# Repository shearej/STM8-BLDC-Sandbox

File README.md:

# STM8-BLDC-Sandbox
BLDC Project

This is meant as a playground of sorts to be later fully integrated into the Logikos BLDC motor project.

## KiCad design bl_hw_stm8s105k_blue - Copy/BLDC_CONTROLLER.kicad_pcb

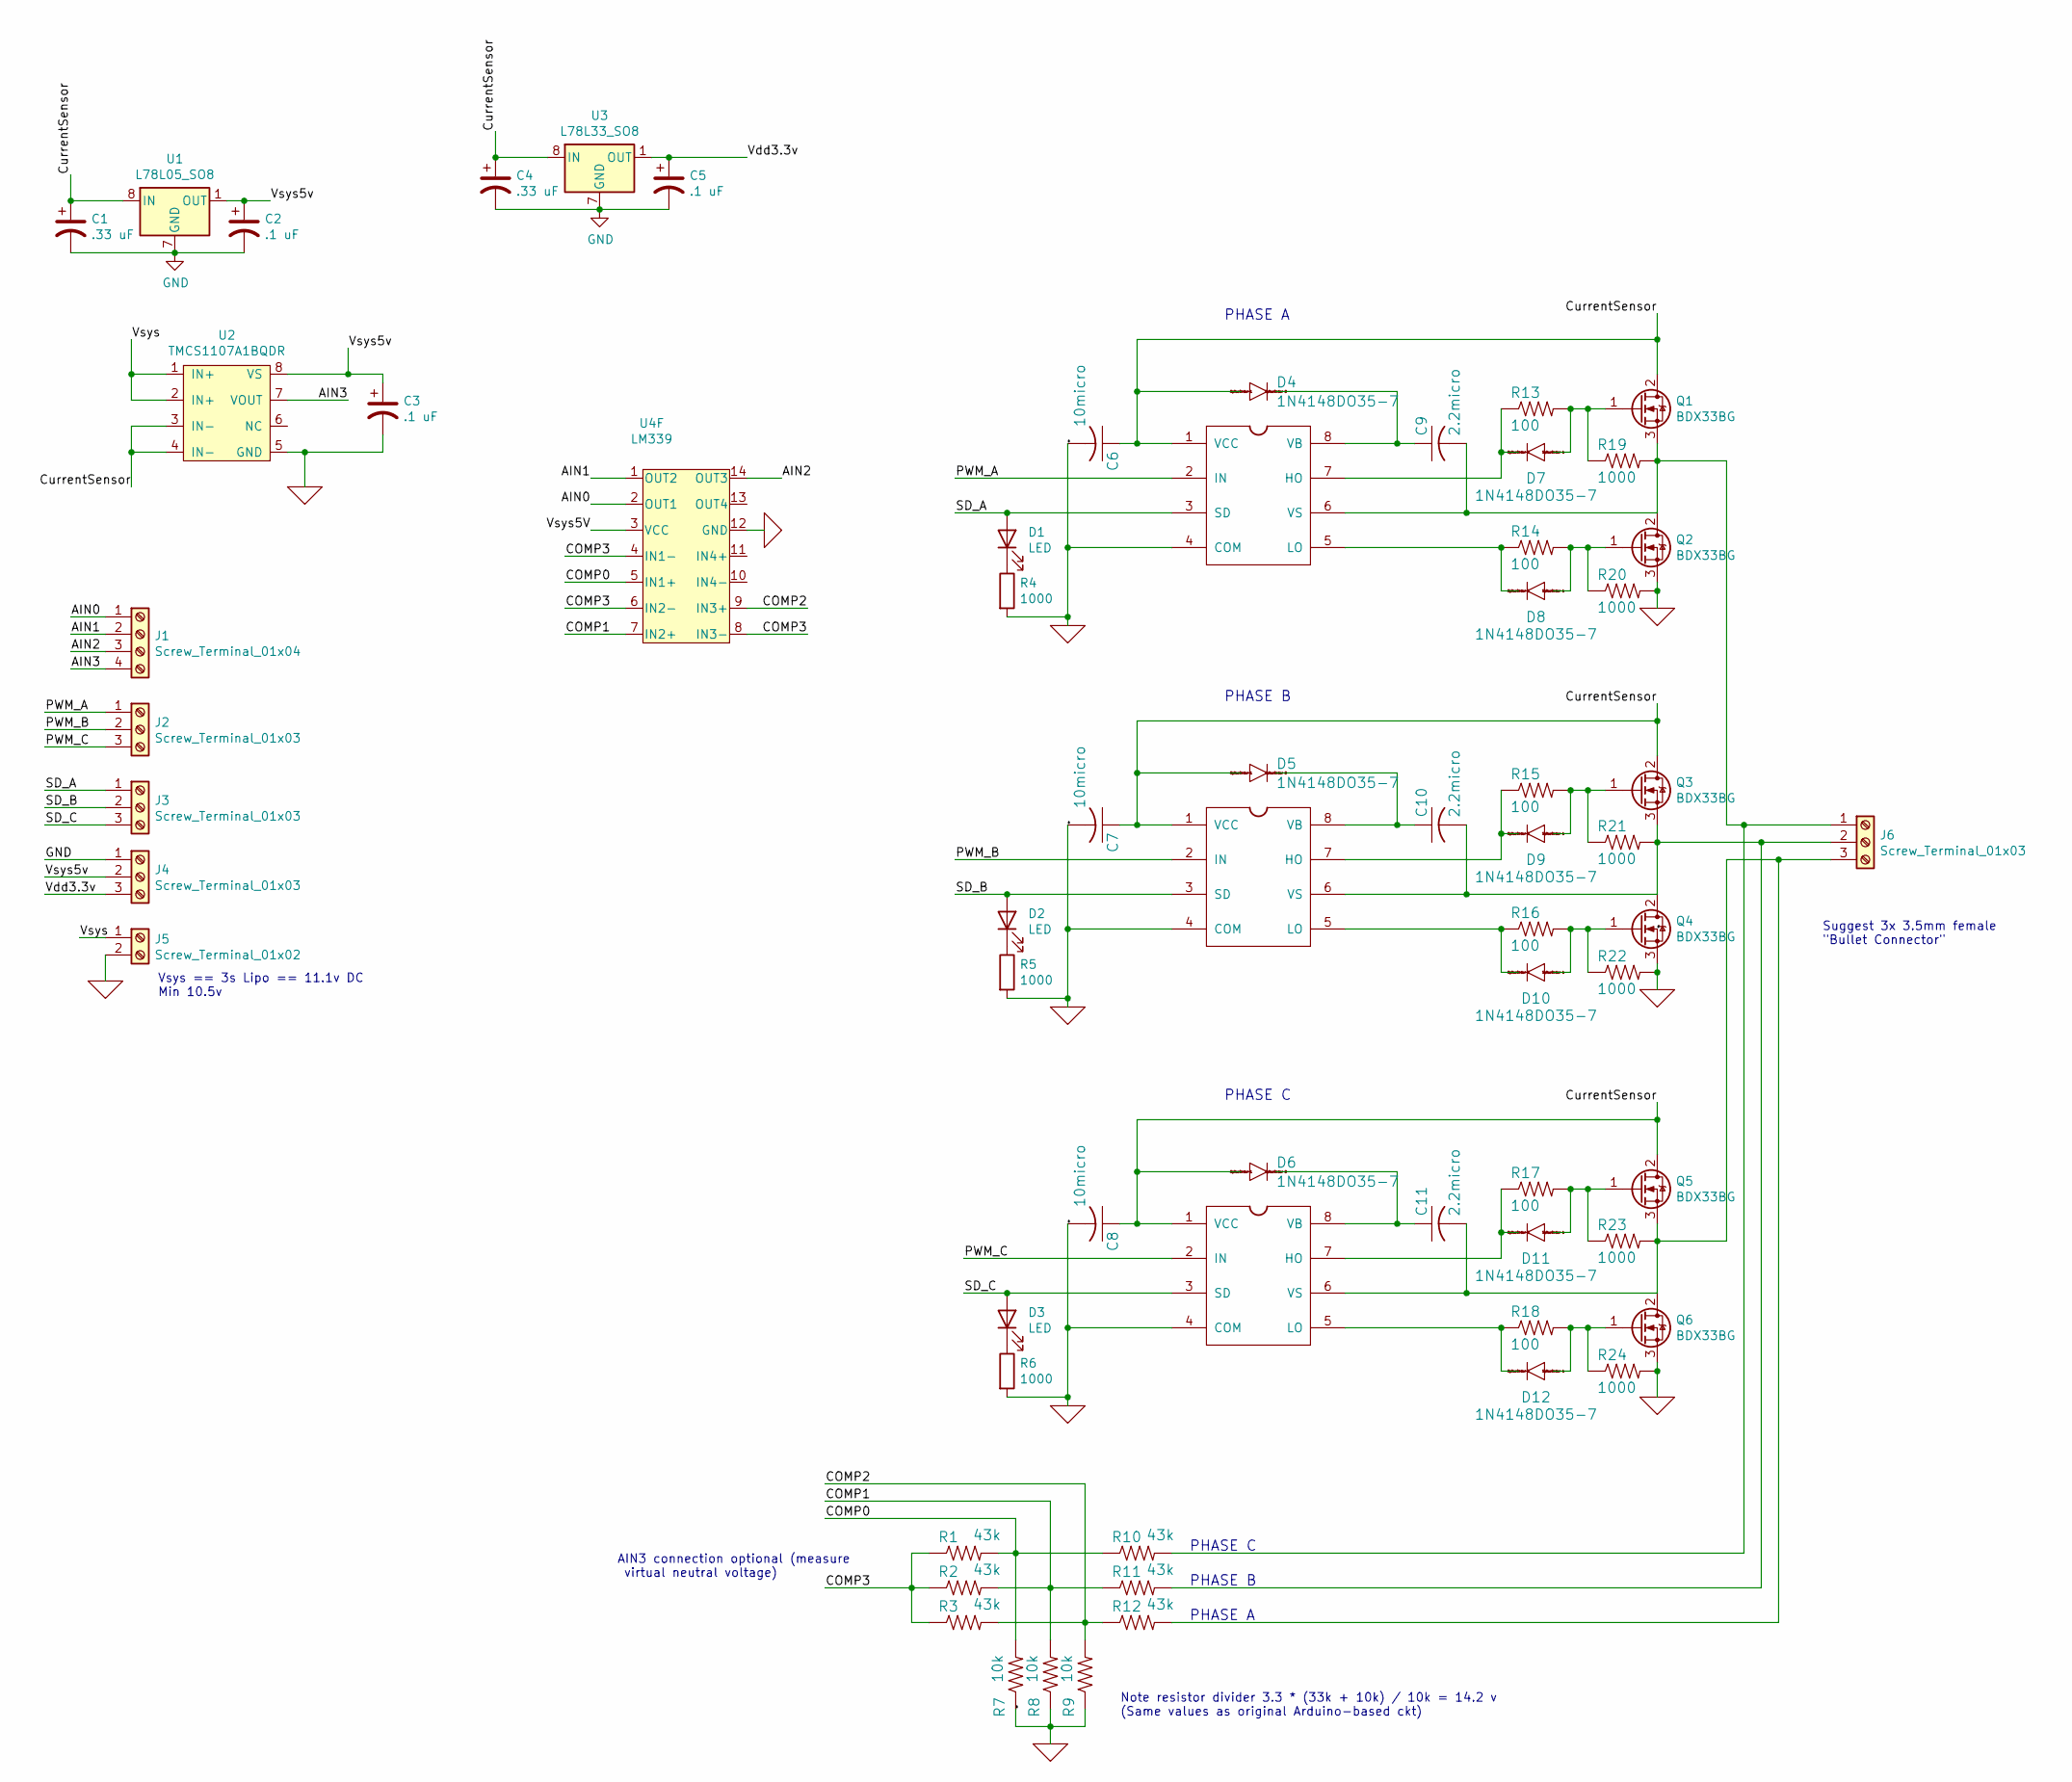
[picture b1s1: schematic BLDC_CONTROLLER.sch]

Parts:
C1, C4: .33 uF; CP_Elec_6.3x5.3; JLCPCB C249777
C2, C3, C5: .1 uF; CP_Elec_4x5.4; JLCPCB C271438
C6, C7, C8: 10micro; CP_Elec_4x5.3; JLCPCB C249759
C9, C10, C11: 2.2micro; CP_Elec_3x5.4; JLCPCB C445056
D1, D2, D3: LED; LED_0201_0603Metric; JLCPCB C192316
D4, D5, D6, D7, D8, D9, D10, D11, D12: 1N4148DO35-7; D_SOD-323; JLCPCB C2128
J1: Screw_Terminal_01x04; TerminalBlock_MetzConnect_Type086_RT03404HBLC_1x04_P3.81mm_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; JLCPCB C69809
J2, J6: Screw_Terminal_01x03; TerminalBlock_Phoenix_MKDS-1,5-3-5.08_1x03_P5.08mm_Horizont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; JLCPCB C72334
J3, J4: Screw_Terminal_01x03; TerminalBlock_Phoenix_MKDS-1,5-3_1x03_P5.00mm_Horizontal
J5: Screw_Terminal_01x02; TerminalBlock_Phoenix_MKDS-1,5-2-5.08_1x02_P5.08mm_Horizont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; JLCPCB C92150
Q1, Q2, Q3, Q4, Q5, Q6: BDX33BG; TO-220-3_Vertical; JLCPCB C152522
R1, R2, R3, R10, R11, R12: 43k; R_0603_1608Metric; JLCPCB C23172
R4, R5, R6, R19, R20, R21, R22, R23, R24: 1000; R_0402_1005Metric; JLCPCB C11702
R7, R8, R9: 10k; R_0402_1005Metric; JLCPCB C25744
R13, R14, R15, R16, R17, R18: 100; R_0603_1608Metric; JLCPCB C22775
U1: L78L05_SO8; SOIC-8_3.9x4.9mm_P1.27mm; JLCPCB C81363
U2: TMCS1107A1BQDR; SOIC-8_3.9x4.9mm_P1.27mm
U3: L78L33_SO8; SOIC-8_3.9x4.9mm_P1.27mm; JLCPCB C86187
U4: LM339; TSSOP-14_4.4x5mm_P0.65mm; JLCPCB C111178
U$1, U$2, U$3: IR2104S; SOIC-8_3.9x4.9mm_P1.27mm; JLCPCB C2960

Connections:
/AIN0: J1.1, U4.2
/AIN1: J1.2, U4.1
/AIN2: J1.3, U4.14
/AIN3: J1.4, U2.7 (VOUT)
/COMP0: R1.2, R7.2, R10.1, U4.5 (+)
/COMP1: R2.2, R8.2, R11.1, U4.7 (+)
/COMP2: R3.2, R9.2, R12.1, U4.9 (+)
/COMP3: R1.1, R2.1, R3.1, U4.4 (-), U4.6 (-), U4.8 (-)
/CurrentSensor: C1.1, C4.1, C6.1, C7.1, C8.1, D4.2 (A), D5.2 (A), D6.2 (A), Q1.2 (D), Q3.2 (D), Q5.2 (D), U1.8 (IN), U2.3 (IN-), U2.4 (IN-), U3.8 (IN), U$1.1 (VCC), U$2.1 (VCC), U$3.1 (VCC)
/PWM_A: J2.1, U$1.2 (IN)
/PWM_B: J2.2, U$2.2 (IN)
/PWM_C: J2.3, U$3.2 (IN)
/SD_A: D1.2 (A), J3.1, U$1.3 (SD)
/SD_B: D2.2 (A), J3.2, U$2.3 (SD)
/SD_C: D3.2 (A), J3.3, U$3.3 (SD)
/Vdd3.3v: C5.1, J4.3, U3.1 (OUT)
/Vsys: J5.1, U2.1 (IN+), U2.2 (IN+)
/Vsys5V: U4.3 (V+)
/Vsys5v: C2.1, C3.1, J4.2, U1.1 (OUT), U2.8 (VS)
unnamed: C9.1, D4.1 (C), U$1.8 (VB)
unnamed: C9.2, J6.1, Q1.3 (S), Q2.2 (D), R10.2, R19.2, U$1.6 (VS)
unnamed: C10.1, D5.1 (C), U$2.8 (VB)
unnamed: C10.2, J6.2, Q3.3 (S), Q4.2 (D), R11.2, R21.2, U$2.6 (VS)
unnamed: C11.1, D6.1 (C), U$3.8 (VB)
unnamed: C11.2, J6.3, Q5.3 (S), Q6.2 (D), R12.2, R23.2, U$3.6 (VS)
unnamed: D1.1 (K), R4.1
unnamed: D2.1 (K), R5.1
unnamed: D3.1 (K), R6.1
unnamed: D7.1 (C), R13.1, U$1.7 (HO)
unnamed: D7.2 (A), Q1.1 (G), R13.2, R19.1
unnamed: D8.1 (C), R14.1, U$1.5 (LO)
unnamed: D8.2 (A), Q2.1 (G), R14.2, R20.1
unnamed: D9.1 (C), R15.1, U$2.7 (HO)
unnamed: D9.2 (A), Q3.1 (G), R15.2, R21.1
unnamed: D10.1 (C), R16.1, U$2.5 (LO)
unnamed: D10.2 (A), Q4.1 (G), R16.2, R22.1
unnamed: D11.1 (C), R17.1, U$3.7 (HO)
unnamed: D11.2 (A), Q5.1 (G), R17.2, R23.1
unnamed: D12.1 (C), R18.1, U$3.5 (LO)
unnamed: D12.2 (A), Q6.1 (G), R18.2, R24.1

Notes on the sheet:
PHASE C
PHASE B
PHASE A
Note resistor divider 3.3 * (33k + 10k) / 10k = 14.2 v (Same values as original Arduino-based ckt)
Suggest 3x 3.5mm female "Bullet Connector"
AIN3 connection optional (measure virtual neutral voltage)
Vsys == 3s Lipo == 11.1v DC Min 10.5v

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
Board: 2 copper layers, 66 parts (0 on the bottom side), 41 nets, no tracks yet.

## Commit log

2021-05-17 Add data logger
2021-05-18 Changed file locations
2021-05-18 Re-basing files
2021-05-18 Updated README.md Changed pointers in sendData removed SOF from struct and put it in sendData
2021-05-20 Simplified sendData function
2021-05-21 Update bit order for input
2021-05-21 Improved sendData pointer indexing
2021-05-21 Added SCILAB.sce
2021-05-21 Added Data
2021-05-24 UI/Plotting prototype added
2021-05-25 Updated UI
2021-07-16 Added PCB Schematic
